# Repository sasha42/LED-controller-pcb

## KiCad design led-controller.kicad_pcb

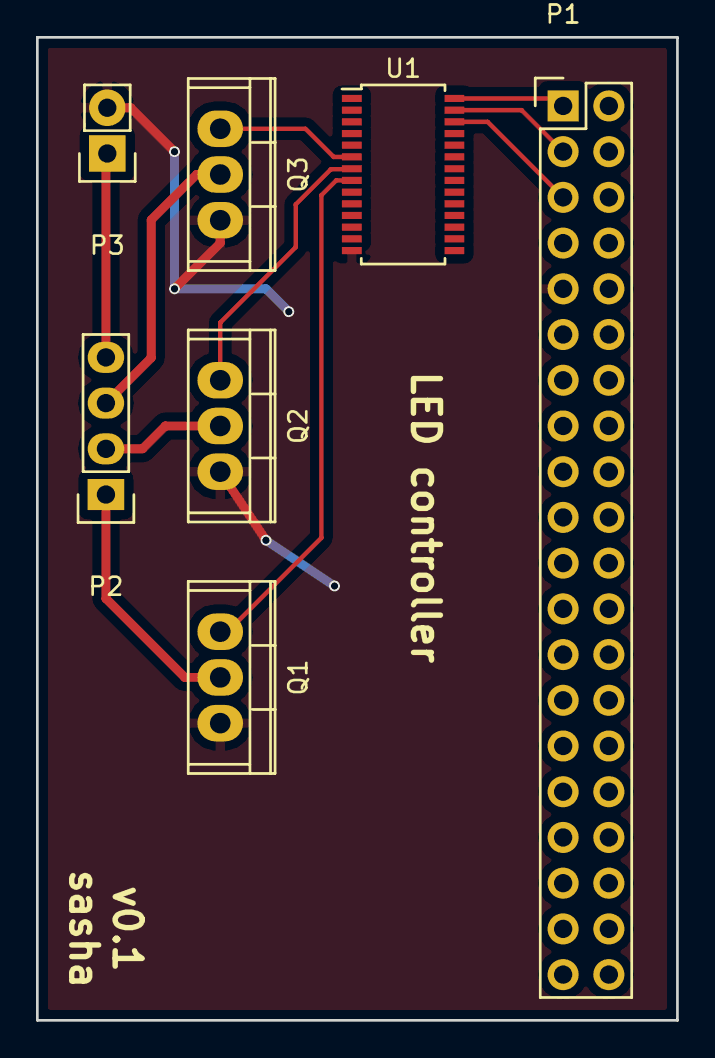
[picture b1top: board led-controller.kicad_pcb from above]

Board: 2 copper layers, 35.6 x 54.6 mm, 7 parts (0 on the bottom side), 11 nets.

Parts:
P1: CONN_02X20; Pin_Header_Straight_2x20
P2: CONN_01X04; Pin_Header_Straight_1x04
P3: CONN_01X02; Pin_Header_Straight_1x02
Q1, Q2, Q3: IRF540N; TO-220
U1: PCA9685-TSSOP; TSSOP-28_4.4x9.7mm_Pitch0.65mm

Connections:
GND: P1.9, P3.2, Q1.3, Q2.3, Q3.3, U1.14
unnamed: P1.1, U1.28
unnamed: P1.3, U1.27
unnamed: P1.5, U1.26
unnamed: P2.1, Q1.2
unnamed: P2.2, Q2.2
unnamed: P2.3, Q3.2
unnamed: P2.4, P3.1
unnamed: Q1.1, U1.8
unnamed: Q2.1, U1.7
unnamed: Q3.1, U1.6

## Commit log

2017-08-14 initial commit sent to pcb fab
2017-10-11 added to schema more transistors and dc dc converter
2017-10-15 added images
